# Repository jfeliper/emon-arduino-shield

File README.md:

# emon-arduino-shield
Estudiando la electrónica de Open Energy Monitor

Shield para arduino UNO

En el directorio eagle están los proyectos en formato eagle tal como podemos descargarlos de https://github.com/openenergymonitor
También tenemos dichos proyectos importados en kicad

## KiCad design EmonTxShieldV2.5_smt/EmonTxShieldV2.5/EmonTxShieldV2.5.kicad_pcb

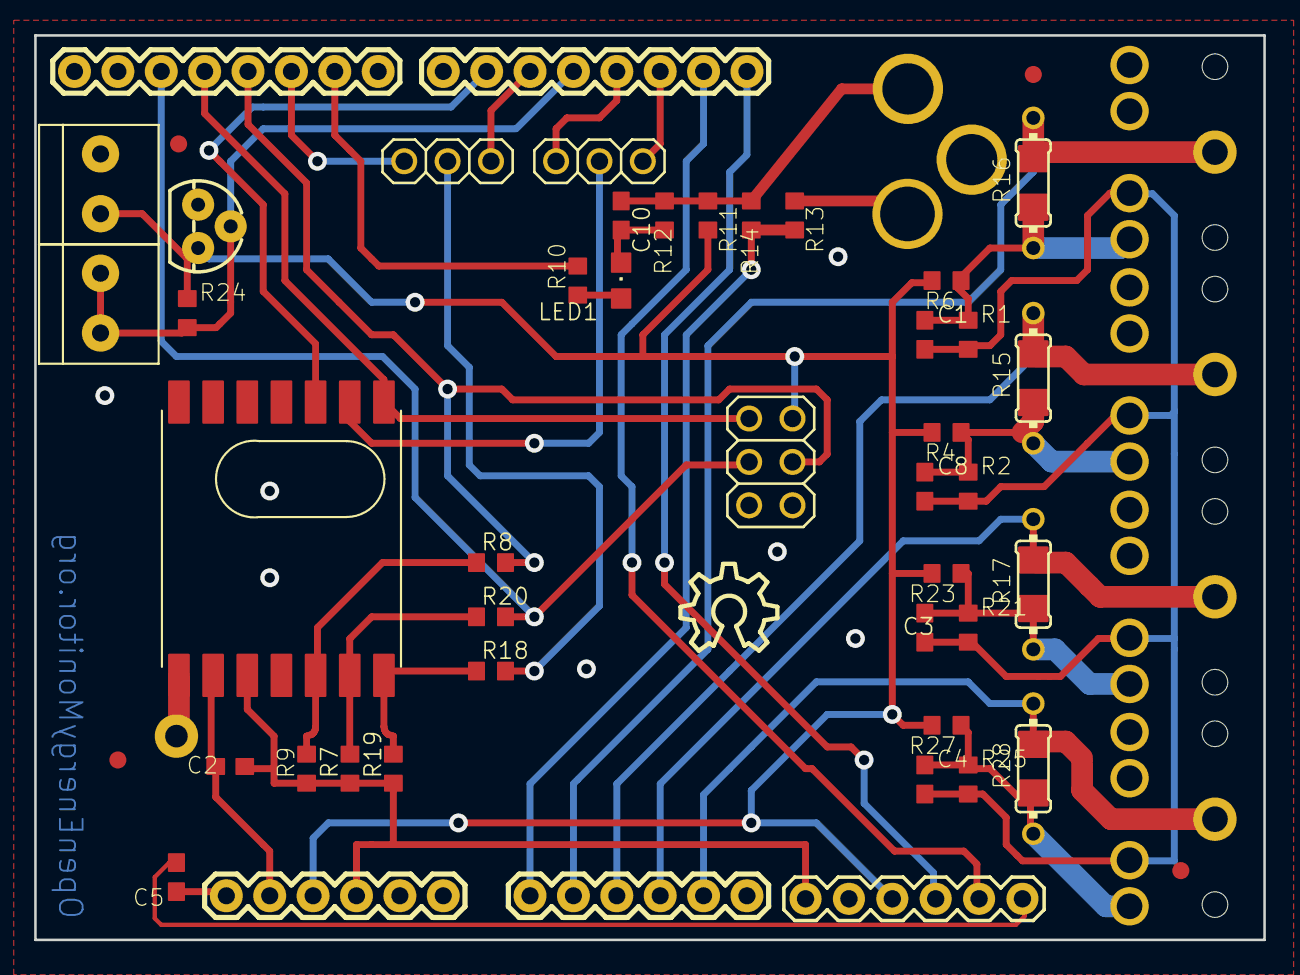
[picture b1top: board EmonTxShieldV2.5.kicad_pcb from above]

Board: 2 copper layers, 72.0 x 53.0 mm, 56 parts (0 on the bottom side), 35 nets.

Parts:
AC9V1: POWER_JACKPTH_LOCK; POWER_JACK_PTH_LOCK
ANT1: ANTENNA; PAD-01
ARDUINO1: ARDUINO2
C1, C3, C4, C8, C10: 10µ; C0603
C2, C5: 100nF; C0603
CT1, CT2, CT3, CT4: STEREOJACK; STX3100
ISP1: 3x2F - BOTTOM; 2X03
J1, J2: 1X2-3.5MM
JP1, JP2: PINHD-1X3; 1X03
JP3: FTDI_BASICPTH; FTDI_BASIC
LED1: green; CHIPLED_0805
LOGO1: OSHW_LOGO_10MILX0200-NT; OSHW_10X200_NOTEXT
Q2: DS18B20; TO-92
R1, R2, R4, R6, R11, R12, R21, R23, R25, R27: 470K; R0603
R3, R5, R22, R26: 33R; 0204_7
R7, R9, R19: 10k; R0603
R8, R18, R20: 4k7; R0603
R10: 1K; R0603
R13: 120K; R0603
R14: 10K; R0603
R15, R16, R17, R28: 33R; R1206
R24: 4K7; R0603
U$1, U$3, U$4, U$5: FIDUCIAL; FIDUCIAL_1MM
U$2: RFM12B

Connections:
3.3V: ARDUINO1.3V3, C2.1, U$2.VDD
+5V: ARDUINO1.5V, ISP1.2, J1.1, JP3.VCC, Q2.3, R4.2, R6.2, R11.2, R23.2, R24.1, R27.2
/ADC0: ARDUINO1.0, R13.2, R14.1
/ADC1: ARDUINO1.1, CT1.1, R5.2, R16.2
/ADC2: ARDUINO1.2, CT2.1, R3.2, R15.2
/ADC3: ARDUINO1.3, CT3.1, R17.2, R22.2
/ADC4: ARDUINO1.4, CT4.1, R26.2, R28.2
/DIG2: ARDUINO1.02, JP2.1
/DIG3: ARDUINO1.PWM_03, JP2.3
/DIG4: ARDUINO1.04, J2.1, J2.2, Q2.2, R24.2
/DIG5: ARDUINO1.PWM_05, JP1.3
/DIG6: ARDUINO1.PWM_06, U$2.FFS
/DIG9: ARDUINO1.PWM_09, R10.2
/DIG10: ARDUINO1.PWM_10, JP1.1
/MISO: ARDUINO1.12, ISP1.1, U$2.SDO
/MOSI: ARDUINO1.PWM_11, ISP1.4, R8.2
/RST: ARDUINO1.RESET, C5.1
/RX: ARDUINO1.RX_00, JP3.TXO
/SCK: ARDUINO1.13, ISP1.3, R20.2
/TX: ARDUINO1.TX_01, JP3.RXI
GND: ARDUINO1.GND, C1.2, C2.2, C3.2, C4.2, C8.2, C10.2, CT1.4, CT2.4, CT3.4, CT4.4, ISP1.6, J1.2, JP3.GND, LED1.C, Q2.1, R1.2, R2.2, R7.1, R9.1, R12.1, R19.1, R21.2, R25.2, U$2.GND
unnamed: AC9V1.GND, C10.1, R11.1, R12.2, R14.2
unnamed: AC9V1.PWR, R13.1
unnamed: ANT1.1, U$2.ANT
unnamed: C1.1, CT1.5, R1.1, R5.1, R6.1, R16.1
unnamed: C3.1, CT3.5, R17.1, R21.1, R22.1, R23.1
unnamed: C4.1, CT4.5, R25.1, R26.1, R27.1, R28.1
unnamed: C5.2, JP3.DTR
unnamed: C8.1, CT2.5, R2.1, R3.1, R4.1, R15.1
unnamed: JP1.2, R18.2
unnamed: JP2.2, U$2.IRQ
unnamed: LED1.A, R10.1
unnamed: R8.1, R9.2, U$2.SDI
unnamed: R18.1, R19.2, U$2.SEL
unnamed: R7.2, R20.1, U$2.SCK

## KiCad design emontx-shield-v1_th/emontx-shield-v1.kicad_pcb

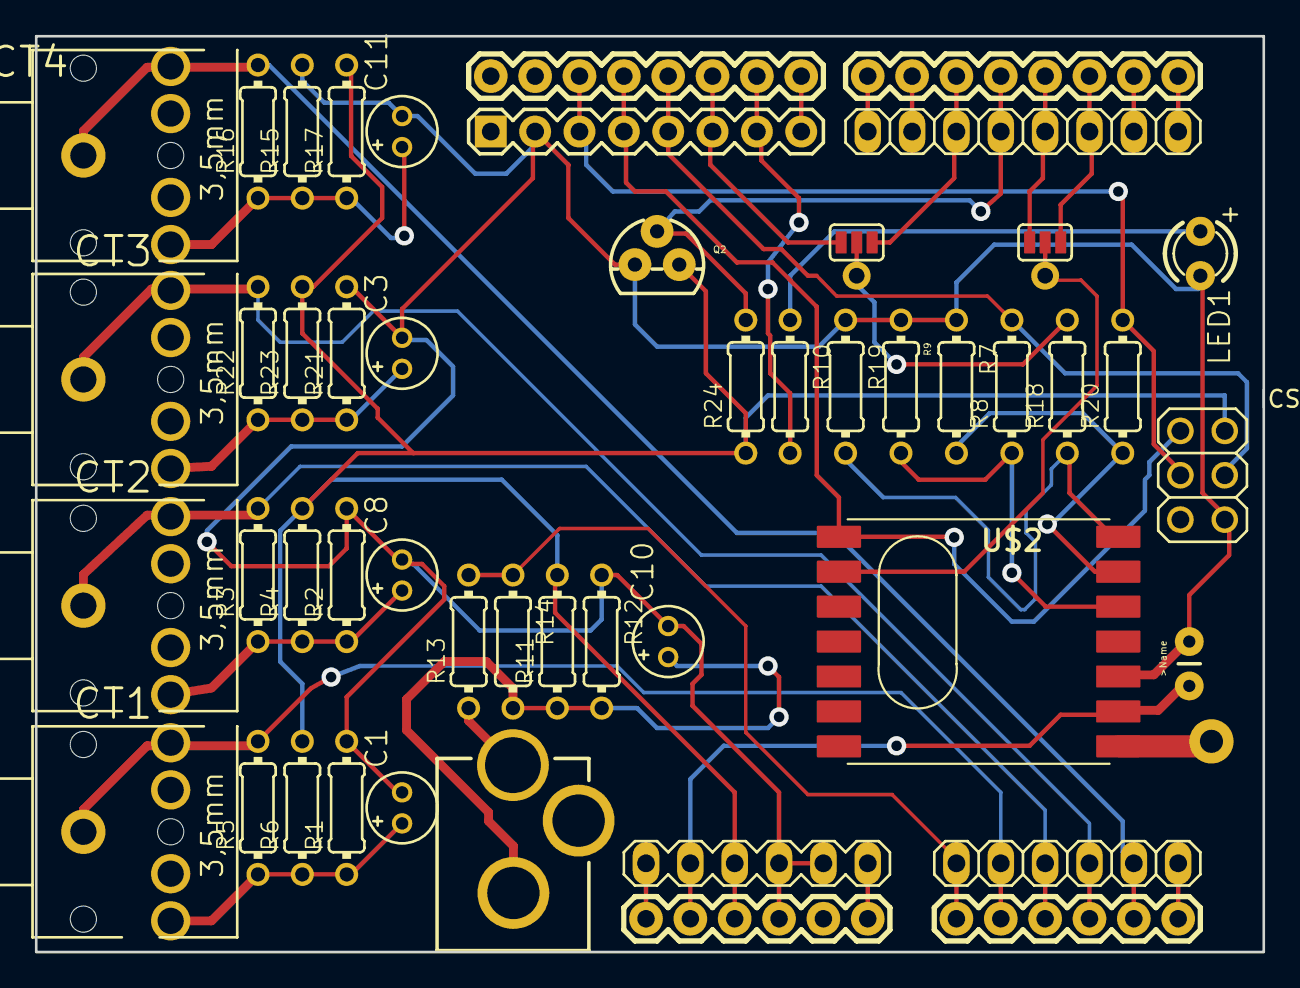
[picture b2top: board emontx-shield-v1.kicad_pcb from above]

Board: 2 copper layers, 70.3 x 52.5 mm, 50 parts (0 on the bottom side), 38 nets.

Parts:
AC9V1: POWER_JACKPTH_LOCK; POWER_JACK_PTH_LOCK
ANT1: ANTENNA; PAD-01
ARDUINO1: ARDUINO2
C1, C3, C8, C10, C11: 10µ; E1,8-4
C2: 0.1µ; CAP-PTH-SMALL
CT1, CT2, CT3, CT4: STEREOJACK; STX3100
ICSP1: 3x2F - BOTTOM; 2X03
JP1: JEELABS_MA06-1
JP2: PINHD-1X8; 1X08
JP3: PINHD-1X6; 1X06
JP6: SPARKFUN_M08; SPARKFUN_1X08
LED1: LED3MM
LOGO1: OSHW_LOGO_10MILX0200-NT; OSHW_10X200_NOTEXT
PAD1, PAD2: JEELABS_1,6_0,8
Q2: DS18B20; TO-92
R1, R2, R4, R6, R11, R12, R15, R17, R21, R23: 470K; 0204_7
R3, R5, R16, R22: 33R; 0204_7
R7, R9, R19: 10k; RESISTOR_0204_7
R8, R18, R20: 4k7; RESISTOR_0204_7
R10: 470R; 0204_7
R13: 100K; 0204_7
R14: 10K; 0204_7
R24: 4K7; 0204_7
SJ1, SJ2: SOLDERJUMPER_2WAYS; SJ_3
U$2: RFM12B

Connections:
3.3V: ARDUINO1.3V3, C2.1, JP1.5, U$2.VDD
+5V: ARDUINO1.5V, ICSP1.2, JP1.4, Q2.3, R4.2, R6.2, R11.2, R17.2, R23.2, R24.1
/ADC0: ARDUINO1.0, JP3.1, R13.2, R14.1
/ADC1: ARDUINO1.1, CT1.1, JP3.2, R5.2
/ADC2: ARDUINO1.2, CT2.1, JP3.3, R3.2
/ADC3: ARDUINO1.3, CT3.1, JP3.4, R22.2
/ADC4: ARDUINO1.4, CT4.1, JP3.5, R16.2
/ADC5: ARDUINO1.5, JP3.6
/DIG2: ARDUINO1.02, JP2.6, SJ2.3
/DIG3: ARDUINO1.PWM_03, JP2.5, SJ2.1
/DIG4: ARDUINO1.04, JP2.4, Q2.2, R24.2
/DIG5: ARDUINO1.PWM_05, JP2.3, SJ1.3
/DIG6: ARDUINO1.PWM_06, JP2.2
/DIG7: ARDUINO1.07, JP2.1
/DIG8: ARDUINO1.08, JP6.8
/DIG9: ARDUINO1.PWM_09, JP6.7, R10.2
/DIG10: ARDUINO1.PWM_10, JP6.6, SJ1.1
/MISO: ARDUINO1.12, ICSP1.1, JP6.4, U$2.SDO
/MOSI: ARDUINO1.PWM_11, ICSP1.4, JP6.5, R8.2
/RST: ARDUINO1.RESET, JP1.6
/RX: ARDUINO1.RX_00, JP2.8
/SCK: ARDUINO1.13, ICSP1.3, JP6.3, R20.2
/TX: ARDUINO1.TX_01, JP2.7
/VIN: ARDUINO1.VIN, JP1.1
GND: ARDUINO1.GND, C1.-, C2.2, C3.-, C8.-, C10.-, C11.-, ICSP1.6, JP1.2, JP1.3, JP6.2, LED1.K, Q2.1, R1.2, R2.2, R7.1, R9.1, R12.1, R15.2, R19.1, R21.2, U$2.GND
unnamed: AC9V1.GND, C10.+, R11.1, R12.2, R14.2
unnamed: AC9V1.PWR, R13.1
unnamed: ANT1.1, U$2.ANT
unnamed: C1.+, CT1.5, R1.1, R5.1, R6.1
unnamed: C3.+, CT3.5, R21.1, R22.1, R23.1
unnamed: C8.+, CT2.5, R2.1, R3.1, R4.1
unnamed: C11.+, CT4.5, R15.1, R16.1, R17.1
unnamed: LED1.A, R10.1
unnamed: PAD1.1, R18.2, SJ1.2
unnamed: PAD2.1, SJ2.2, U$2.IRQ
unnamed: R8.1, R9.2, U$2.SDI
unnamed: R18.1, R19.2, U$2.SEL
unnamed: R7.2, R20.1, U$2.SCK

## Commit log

2018-07-26 iniciando git en sobremesa ubuntu
2018-07-27 añadidos ficheros originales en formato eagle y convertidos a Kicad en Windows
